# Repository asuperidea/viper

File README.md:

# Viper Devboard

Viper is a custom built devboard by (Simon Crystal)[https://simoncrystal.dev].

Viper uses the ESP32 C6 Mini to supply 14 GPIO pins. Viper also includes a 3.3V, 5V, and two ground pins.

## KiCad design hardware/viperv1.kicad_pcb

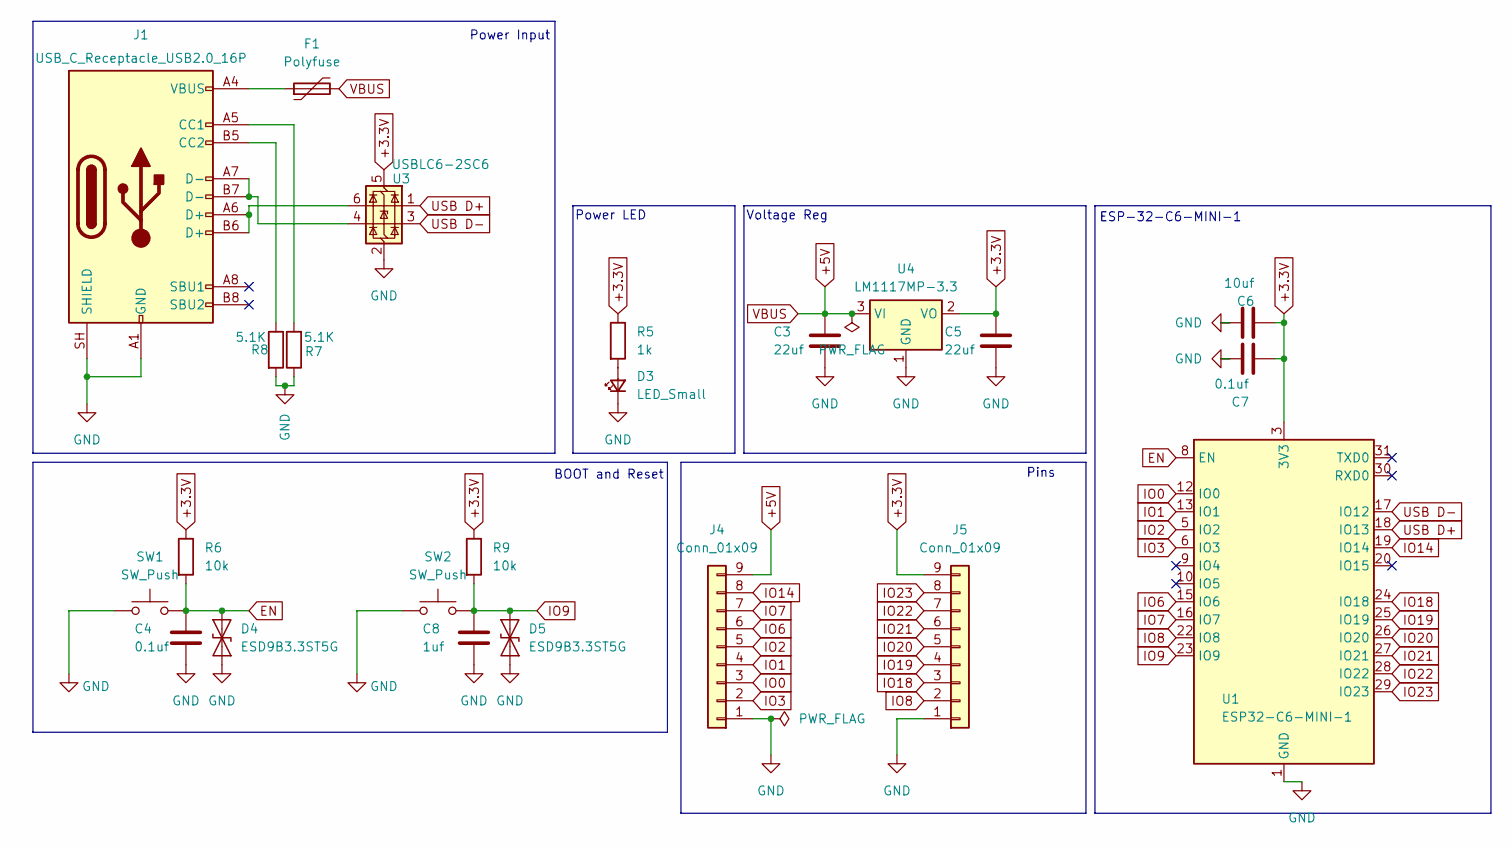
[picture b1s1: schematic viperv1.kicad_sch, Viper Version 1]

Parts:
C3, C5: 22uf; C_0603_1608Metric
C4, C7: 0.1uf; C_0603_1608Metric
C6: 10uf; C_0603_1608Metric
C8: 1uf; C_0603_1608Metric
D3: LED_Small; LED_0603_1608Metric
D4, D5: ESD9B3.3ST5G; D_SOD-923
F1: Polyfuse; Fuse_1206_3216Metric
J1: USB_C_Receptacle_USB2.0_16P; USB_C_Receptacle_HRO_TYPE-C-31-M-12
J4, J5: Conn_01x09; PinHeader_1x09_P2.54mm_Vertical
R5: 1k; R_0603_1608Metric
R6, R9: 10k; R_0603_1608Metric
R7, R8: 5.1K; R_0603_1608Metric
SW1, SW2: SW_Push; SW_Push_1P1T_NO_CK_KMR2
U1: ESP32-C6-MINI-1
U3: USBLC6-2SC6; SOT-23-6
U4: LM1117MP-3.3; SOT-223-3_TabPin2

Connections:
+3.3V: C5.1, C6.2, C7.2, J5.9, R5.1, R6.1, R9.1, U1.3 (3V3), U3.5 (VBUS), U4.2 (VO)
+5V: C3.1, F1.2, J4.9, U4.3 (VI)
EN: C4.1, D4.2 (A2), R6.2, SW1.2, U1.8 (EN)
GND: C3.2, C4.2, C5.2, C6.1, C7.1, C8.2, D3.1 (K), D4.1 (A1), D5.1 (A1), J1.A1 (GND), J1.A12 (GND), J1.B1 (GND), J1.B12 (GND), J1.SH (SHIELD), J4.1, J5.1, R7.1, R8.2, SW1.1, SW2.1, U1.1 (GND), U1.2 (GND), U1.11 (GND), U1.14 (GND), U1.36 (GND), U1.37 (GND), U1.38 (GND), U1.39 (GND), U1.40 (GND), U1.41 (GND), U1.42 (GND), U1.43 (GND), U1.44 (GND), U1.45 (GND), U1.46 (GND), U1.47 (GND), U1.48 (GND), U1.49 (GND), U1.50 (GND), U1.51 (GND), U1.52 (GND), U1.53 (GND), U3.2 (GND), U4.1 (GND)
IO0: J4.3, U1.12 (IO0)
IO1: J4.4, U1.13 (IO1)
IO2: J4.5, U1.5 (IO2)
IO3: J4.2, U1.6 (IO3)
IO6: J4.6, U1.15 (IO6)
IO7: J4.7, U1.16 (IO7)
IO8: J5.2, U1.22 (IO8)
IO9: C8.1, D5.2 (A2), R9.2, SW2.2, U1.23 (IO9)
IO14: J4.8, U1.19 (IO14)
IO18: J5.3, U1.24 (IO18)
IO19: J5.4, U1.25 (IO19)
IO20: J5.5, U1.26 (IO20)
IO21: J5.6, U1.27 (IO21)
IO22: J5.7, U1.28 (IO22)
IO23: J5.8, U1.29 (IO23)
unnamed: D3.2 (A), R5.2
unnamed: F1.1, J1.A4 (VBUS), J1.A9 (VBUS), J1.B4 (VBUS), J1.B9 (VBUS)
unnamed: J1.A5 (CC1), R7.2
unnamed: J1.B5 (CC2), R8.1
unnamed: J1.A6 (D+), J1.B6 (D+), U3.6 (I/O1)
unnamed: J1.A7 (D-), J1.B7 (D-), U3.4 (I/O2)
USB D+: U1.18 (IO13), U3.1 (I/O1)
USB D-: U1.17 (IO12), U3.3 (I/O2)

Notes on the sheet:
BOOT and Reset
ESP-32-C6-MINI-1
Pins
Power Input
Voltage Reg
Power LED

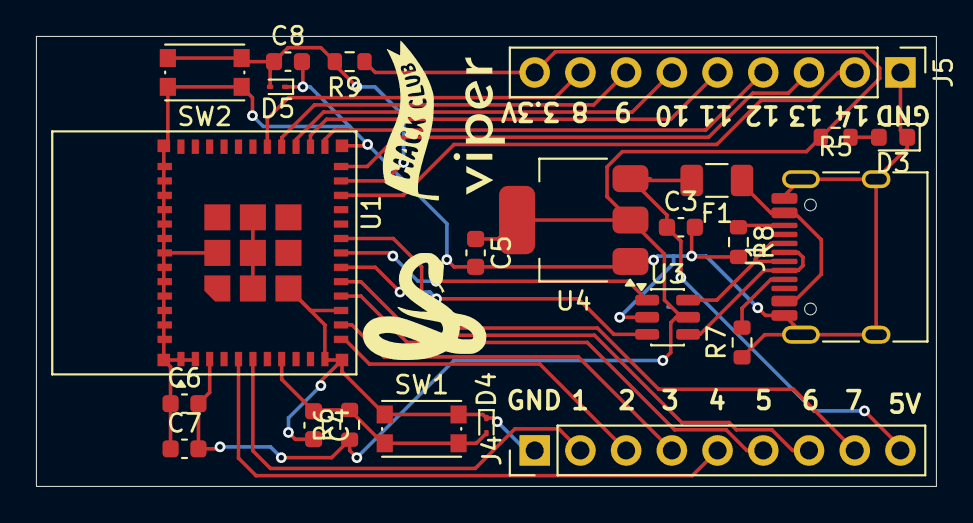
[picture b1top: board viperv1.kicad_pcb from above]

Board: 2 copper layers, 50.0 x 25.0 mm, 23 parts (0 on the bottom side), 27 nets.
